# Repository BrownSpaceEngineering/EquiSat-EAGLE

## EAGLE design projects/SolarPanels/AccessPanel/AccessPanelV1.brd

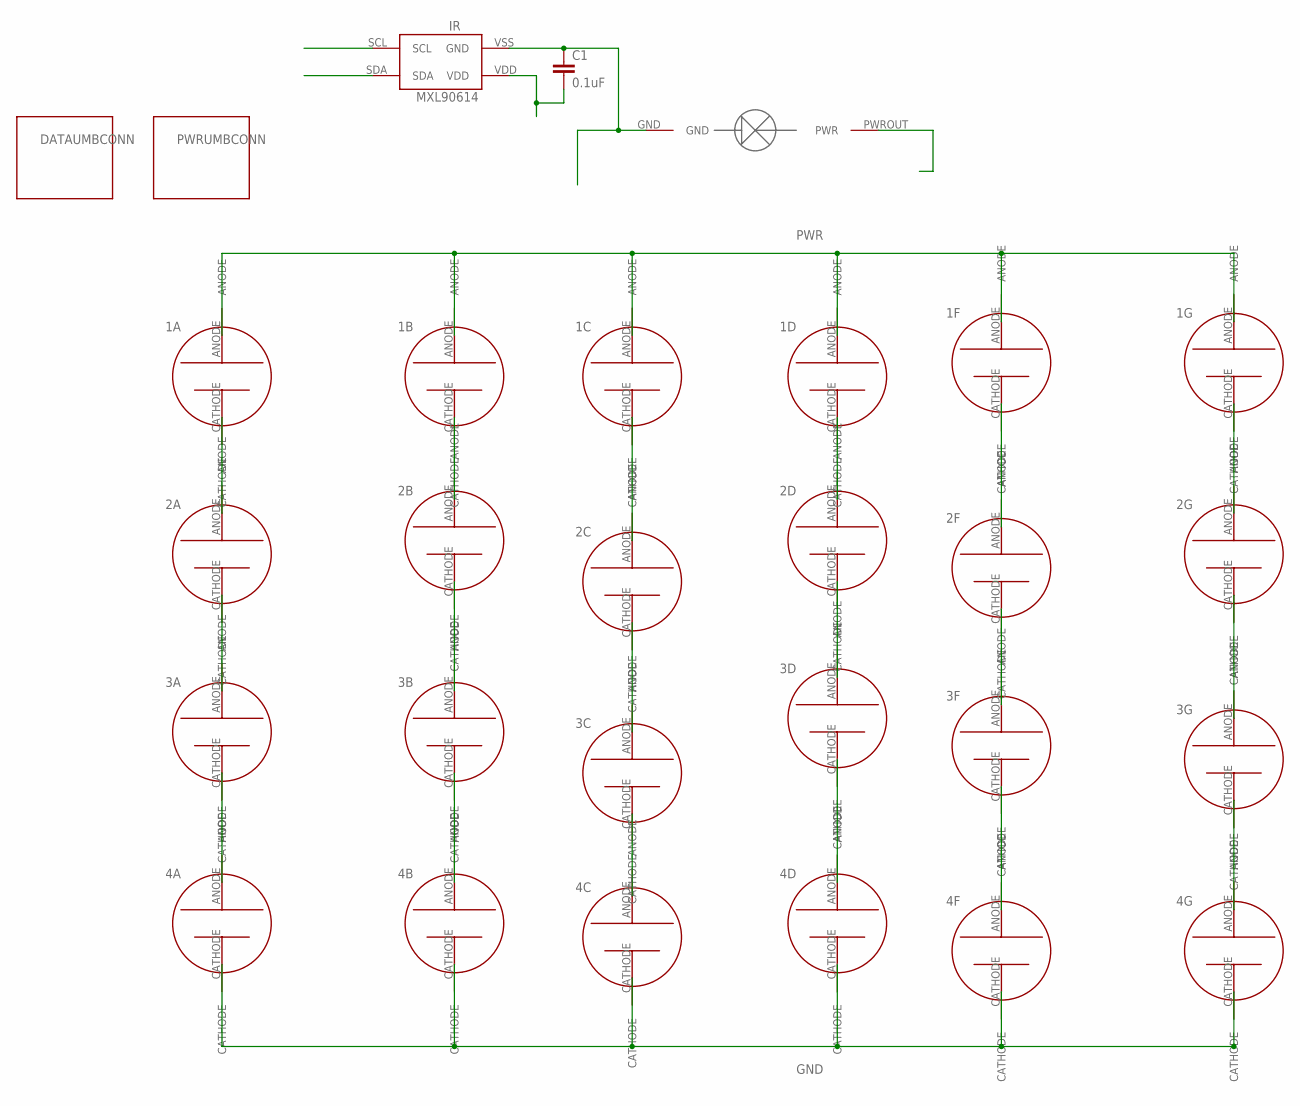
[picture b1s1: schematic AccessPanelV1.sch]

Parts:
1A, 1B, 1C, 1D, 1F, 1G, 2A, 2B, 2C, 2D, 2F, 2G, 3A, 3B, 3C, 3D, 3F, 3G, 4A, 4B, 4C, 4D, 4F, 4G: NEWSOLARPANEL; SOLARCELL2
C1: 0.1uF; 0805
DATAUMBCONN: HARWIN_PWR_BOARDMOUNT
IR: MXL90620; MXL90614
PHD: PHOTODETECTOR; PHOTODECTORDEVICE2
PWRUMBCONN: HARWIN_PWR_BOARDMOUNT

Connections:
3V3: C1.2, IR.VDD
GND: 4A.CATHODE, 4B.CATHODE, 4C.CATHODE, 4D.CATHODE, 4F.CATHODE, 4G.CATHODE, C1.1, IR.VSS (GND), PHD.GND
unnamed: 2A.CATHODE, 3A.ANODE
unnamed: 1C.CATHODE, 2C.ANODE
unnamed: 2B.CATHODE, 3B.ANODE
unnamed: 2C.CATHODE, 3C.ANODE
unnamed: 2D.CATHODE, 3D.ANODE
unnamed: 3C.CATHODE, 4C.ANODE
unnamed: 2F.CATHODE, 3F.ANODE
unnamed: 1B.CATHODE, 2B.ANODE
unnamed: 2G.CATHODE, 3G.ANODE
unnamed: 3G.CATHODE, 4G.ANODE
unnamed: 1D.CATHODE, 2D.ANODE
unnamed: 3F.CATHODE, 4F.ANODE
unnamed: 3D.CATHODE, 4D.ANODE
unnamed: 3B.CATHODE, 4B.ANODE
unnamed: 3A.CATHODE, 4A.ANODE
unnamed: 1A.CATHODE, 2A.ANODE
unnamed: 1G.CATHODE, 2G.ANODE
unnamed: 1F.CATHODE, 2F.ANODE
PDOUT: PHD.PWROUT (PWR)
PWR: 1A.ANODE, 1B.ANODE, 1C.ANODE, 1D.ANODE, 1F.ANODE, 1G.ANODE
SCL: IR.SCL
SDA: IR.SDA

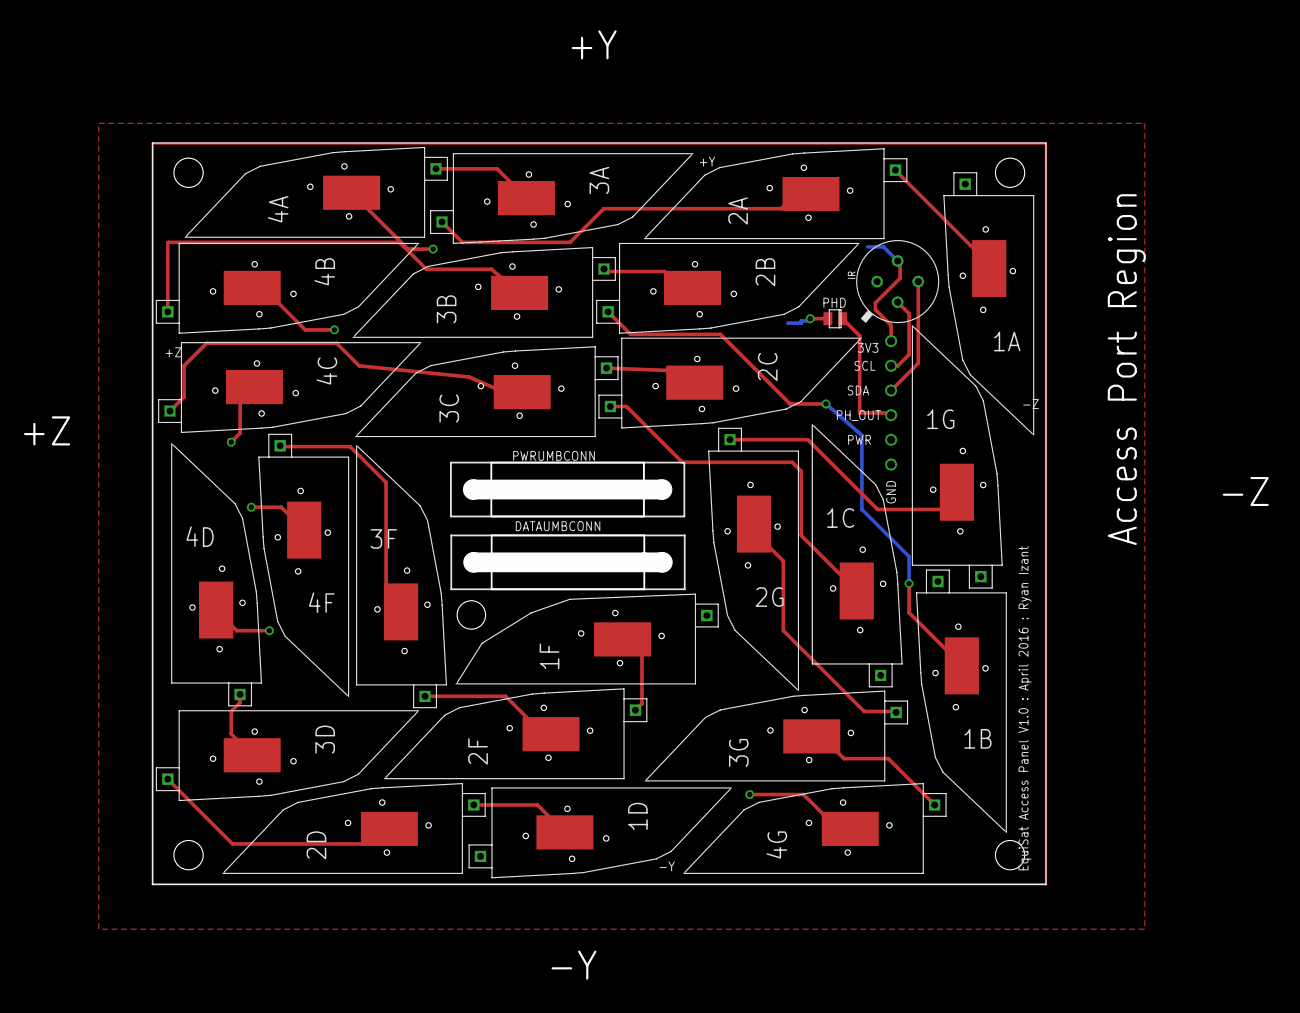
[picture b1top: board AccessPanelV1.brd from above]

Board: 2 copper layers, 99.5 x 82.6 mm, 29 parts (1 on the bottom side), 21 nets.

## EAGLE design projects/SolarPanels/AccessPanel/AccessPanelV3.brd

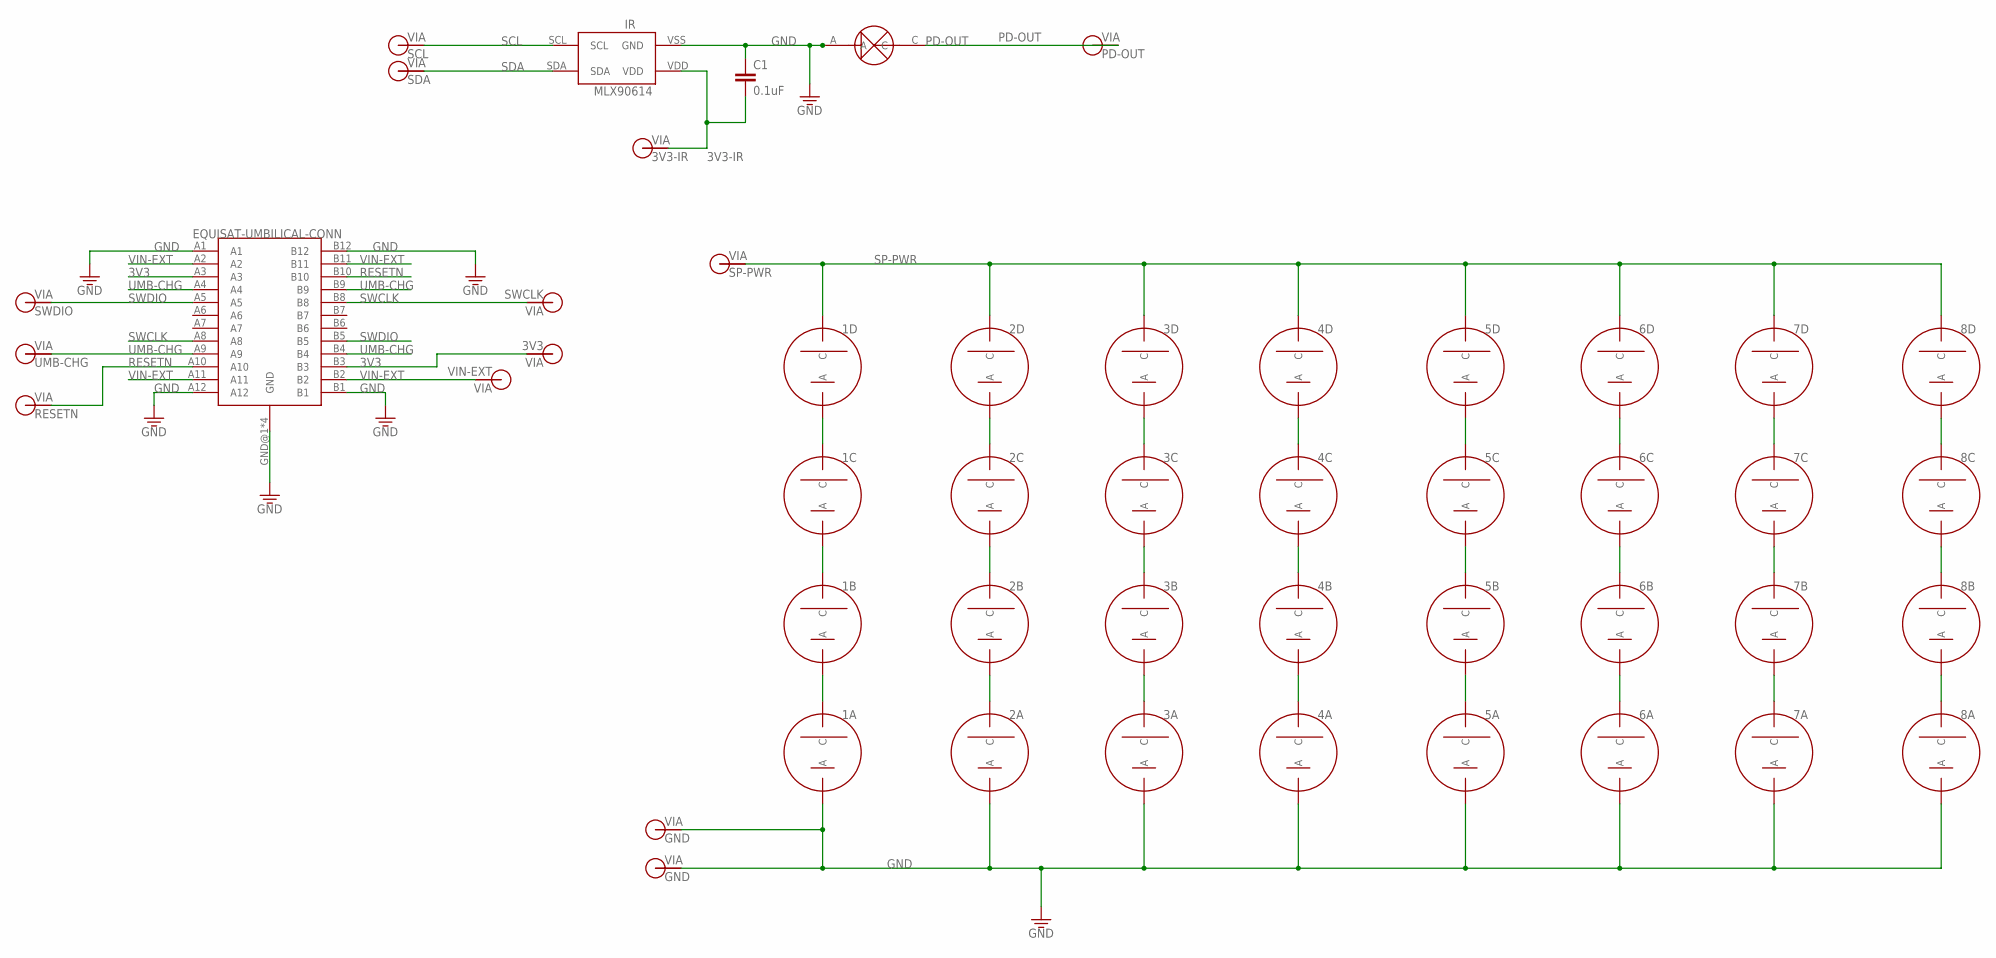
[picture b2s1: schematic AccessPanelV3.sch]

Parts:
1A, 1B, 1C, 1D, 2A, 2B, 2C, 2D, 3A, 3B, 3C, 3D, 4A, 4B, 4C, 4D, 5A, 5B, 5C, 5D, 6A, 6B, 6C, 6D, 7A, 7B, 7C, 7D, 8A, 8B, 8C, 8D: SOLARCELLV3; TRISOLX-V3
C1: 0.1uF; 0805
IR: MXL90614; MXL90620
PD: TEMD6200
SCL: SCL; VIA-60MIL
SDA: SDA; VIA-60MIL
UMB-CONN: EQUISAT-UMBILICAL-CONN; USB-C-RCPT-SMT
V1: SP-PWR; VIA-60MIL
V2, V4: GND; VIA-60MIL
V3: 3V3-IR; VIA-60MIL
V5: UMB-CHG; VIA-60MIL
V6: PD-OUT; VIA-60MIL
V7: VIN-EXT; VIA-60MIL
V8: RESETN; VIA-60MIL
V9: 3V3; VIA-60MIL
V10: SWCLK; VIA-60MIL
V11: SWDIO; VIA-60MIL

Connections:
3V3: UMB-CONN.A3, UMB-CONN.B3, V9.P$1
3V3-IR: C1.2, IR.VDD, V3.P$1
GND: 1A.ANODE (A), 2A.ANODE (A), 3A.ANODE (A), 4A.ANODE (A), 5A.ANODE (A), 6A.ANODE (A), 7A.ANODE (A), 8A.ANODE (A), C1.1, IR.VSS (GND), PD.A, UMB-CONN.A1, UMB-CONN.A12, UMB-CONN.B1, UMB-CONN.B12, UMB-CONN.GND@1 (GND), UMB-CONN.GND@2 (GND), UMB-CONN.GND@3 (GND), UMB-CONN.GND@4 (GND), V2.P$1, V4.P$1
unnamed: 1C.CATHODE (C), 1D.ANODE (A)
unnamed: 2C.CATHODE (C), 2D.ANODE (A)
unnamed: 3C.CATHODE (C), 3D.ANODE (A)
unnamed: 4C.CATHODE (C), 4D.ANODE (A)
unnamed: 5C.CATHODE (C), 5D.ANODE (A)
unnamed: 6C.CATHODE (C), 6D.ANODE (A)
unnamed: 1A.CATHODE (C), 1B.ANODE (A)
unnamed: 2A.CATHODE (C), 2B.ANODE (A)
unnamed: 3A.CATHODE (C), 3B.ANODE (A)
unnamed: 4A.CATHODE (C), 4B.ANODE (A)
unnamed: 5A.CATHODE (C), 5B.ANODE (A)
unnamed: 6A.CATHODE (C), 6B.ANODE (A)
unnamed: 1B.CATHODE (C), 1C.ANODE (A)
unnamed: 2B.CATHODE (C), 2C.ANODE (A)
unnamed: 3B.CATHODE (C), 3C.ANODE (A)
unnamed: 4B.CATHODE (C), 4C.ANODE (A)
unnamed: 5B.CATHODE (C), 5C.ANODE (A)
unnamed: 6B.CATHODE (C), 6C.ANODE (A)
unnamed: 7C.CATHODE (C), 7D.ANODE (A)
unnamed: 7A.CATHODE (C), 7B.ANODE (A)
unnamed: 7B.CATHODE (C), 7C.ANODE (A)
unnamed: 8C.CATHODE (C), 8D.ANODE (A)
unnamed: 8A.CATHODE (C), 8B.ANODE (A)
unnamed: 8B.CATHODE (C), 8C.ANODE (A)
PD-OUT: PD.C, V6.P$1
RESETN: UMB-CONN.A10, UMB-CONN.B10, V8.P$1
SCL: IR.SCL, SCL.P$1
SDA: IR.SDA, SDA.P$1
SP-PWR: 1D.CATHODE (C), 2D.CATHODE (C), 3D.CATHODE (C), 4D.CATHODE (C), 5D.CATHODE (C), 6D.CATHODE (C), 7D.CATHODE (C), 8D.CATHODE (C), V1.P$1
SWCLK: UMB-CONN.A8, UMB-CONN.B8, V10.P$1
SWDIO: UMB-CONN.A5, UMB-CONN.B5, V11.P$1
UMB-CHG: UMB-CONN.A4, UMB-CONN.A9, UMB-CONN.B4, UMB-CONN.B9, V5.P$1
VIN-EXT: UMB-CONN.A2, UMB-CONN.A11, UMB-CONN.B2, UMB-CONN.B11, V7.P$1

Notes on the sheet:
GND
PD-OUT

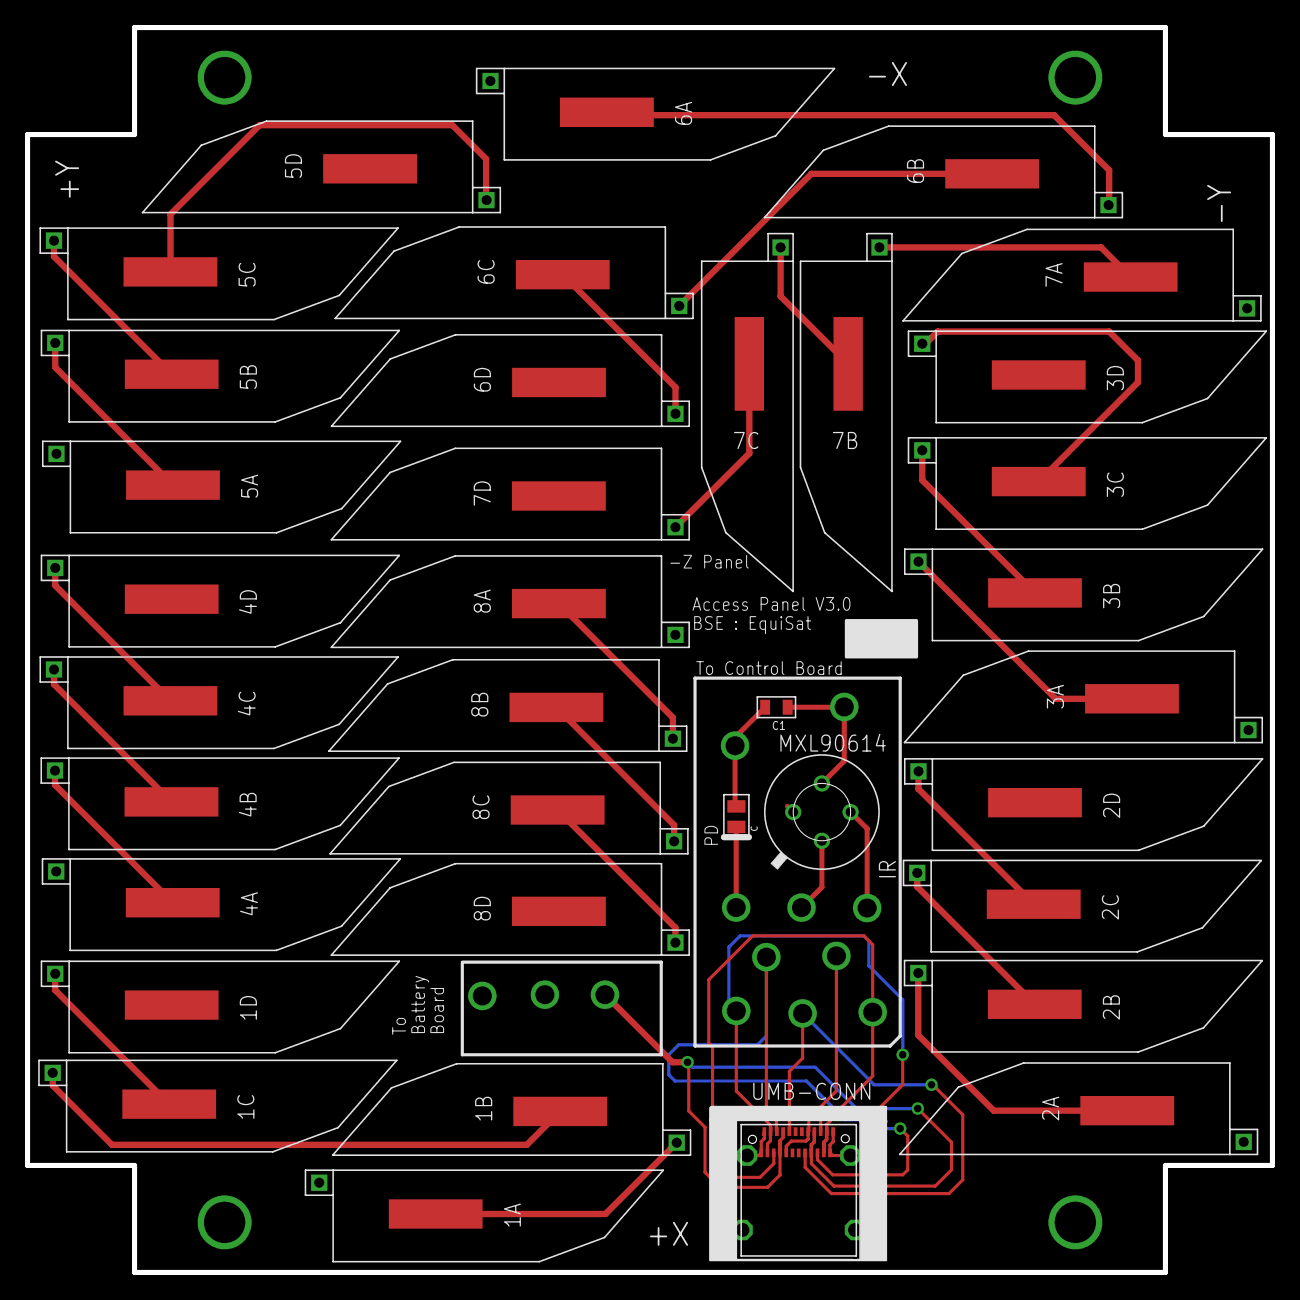
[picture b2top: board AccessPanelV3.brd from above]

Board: 2 copper layers, 99.5 x 99.5 mm, 49 parts (0 on the bottom side), 36 nets.
